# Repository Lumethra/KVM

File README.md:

# KVM
## What is this?

Its a KVM, just there is a catch, it should be a KM, because it doesnt fulfill the criterias for the "V". A KVM is a device that can let you switch the connected USB-devices from one PC to another, so just press or toggle the switch and your mouse and keyboard are connected to the other device, for example a laptop. KVM stands for Keyboard, Video, Mouse and since my thingi only supports USB-devices it only supports keyboards, mice and maybe other usb devices. Thats also why I would call it a KM. 

### Features:
  - 2 USB-C-upstreams
      - for the 2 PC's
  - 4 USB-downstreams
      - 2 USB-C
      - 2 USB-A
  - 1 SL2.1S to bundle the 4 downstreams into 2 pins (D+, D-)
  - 1 Mux to switch between the 2 upstreams for PC switching
  - 1 slider, toggle, switch kinda thingi to set the state

---

## Why?

I thought it would be funny to try that out. It turned out to be quite easy. I also thought about USB3.0 and even USB4.0, but that was too complicated and I settled on USB2.0. A KVM is also sth that you can use in your daily workflow and could turn out to be really handy. 

---

## How??

It was simply replicating the USB-Hub, which I made for my keebs and connecting the upstream to the mux which handles the switching between the 2 USB-C(2.0) to archieve the switching between devices. 

---

## Renders 
> enjoy the raytracing

| PCB with Components | 
| --- |
|  |
|  |

| PCB without Components |
| --- |
|  |
|  |

---

## PCB + Schematics

| Schematics |
| --- |
|  |

| PCB |
| --- |
|  |

---

<details>
  <summary>
    <h2>Zine</h2>
  </summary>

| Zine |
| --- |
|  |

  ---
</details>

## BOM

| Part | Purpose | Cost | Quantity | Total Cost | LCSC/JLCPCB Number | Link |
| --- | --- | --- | --- | --- | --- | --- |
| PCB |connect everything together | $2 | 1(5) | $2 | ~ | [JLCPCB](https://jlcpcb.com) |
| Capacitors | reduce noise in the power | $0.0032 | 8 | $0.0256 | C15849, C14663 | [C15849](https://jlcpcb.com/partdetail/C15849) / [C14663](https://jlcpcb.com/partdetail/C14663) |
| Resistors | prevent things go boom | $0.0016 | 8 | $0.0138 | C23186, C23206 | [C23186](https://jlcpcb.com/partdetail/C23186),[C23206](https://jlcpcb.com/partdetail/C23206) |
| Toggle Switch | say which computer | $0.0579 | 1 | $0.0579 | C431541 | [JLCPCB](https://jlcpcb.com/partdetail/C431541)  |
| USB Mux | change computer (USB) | $0.3720 | 1 | $0.3720 | C42407092 | [JLCPCB](https://jlcpcb.com/partdetail/C42407092)  |
| USB Hub | bundle the downstream | $0.2258 | 1 | $0.2258 | C2684433 | [JLCPCB](https://jlcpcb.com/partdetail/C2684433)  |
| UCB-C | usb connectors | $0.0740 | 4 | $0.2960 | C2765186 | [JLCPCB](https://jlcpcb.com/partdetail/C2765186)  |
| USB-A | usb connectors big | $0.0636 | 2 | $0.1272 | C668591 | [JLCPCB](https://jlcpcb.com/partdetail/C668591)  |

> the prices can change depending on the provider and time <br>
> you can find the JLCPCB parts on [LCSC](https://lcsc.com/) too (exept the PCB) <br>

---

## Contribute

Want to add something?? Want a real KVM with Video? Found any bugs?? Feel free to open a PR (pull request) or an issue. 
> the libraries are all imported with [easyeda2kicad](https://github.com/uPesy/easyeda2kicad.py)

---

## Thank you

A huge thank you to my brain, who didnt die in this session. Another huge thank you to all the guys teaching me hardware. A last thank you to my laptop and kicad who dont like each other and decides to crash alot.

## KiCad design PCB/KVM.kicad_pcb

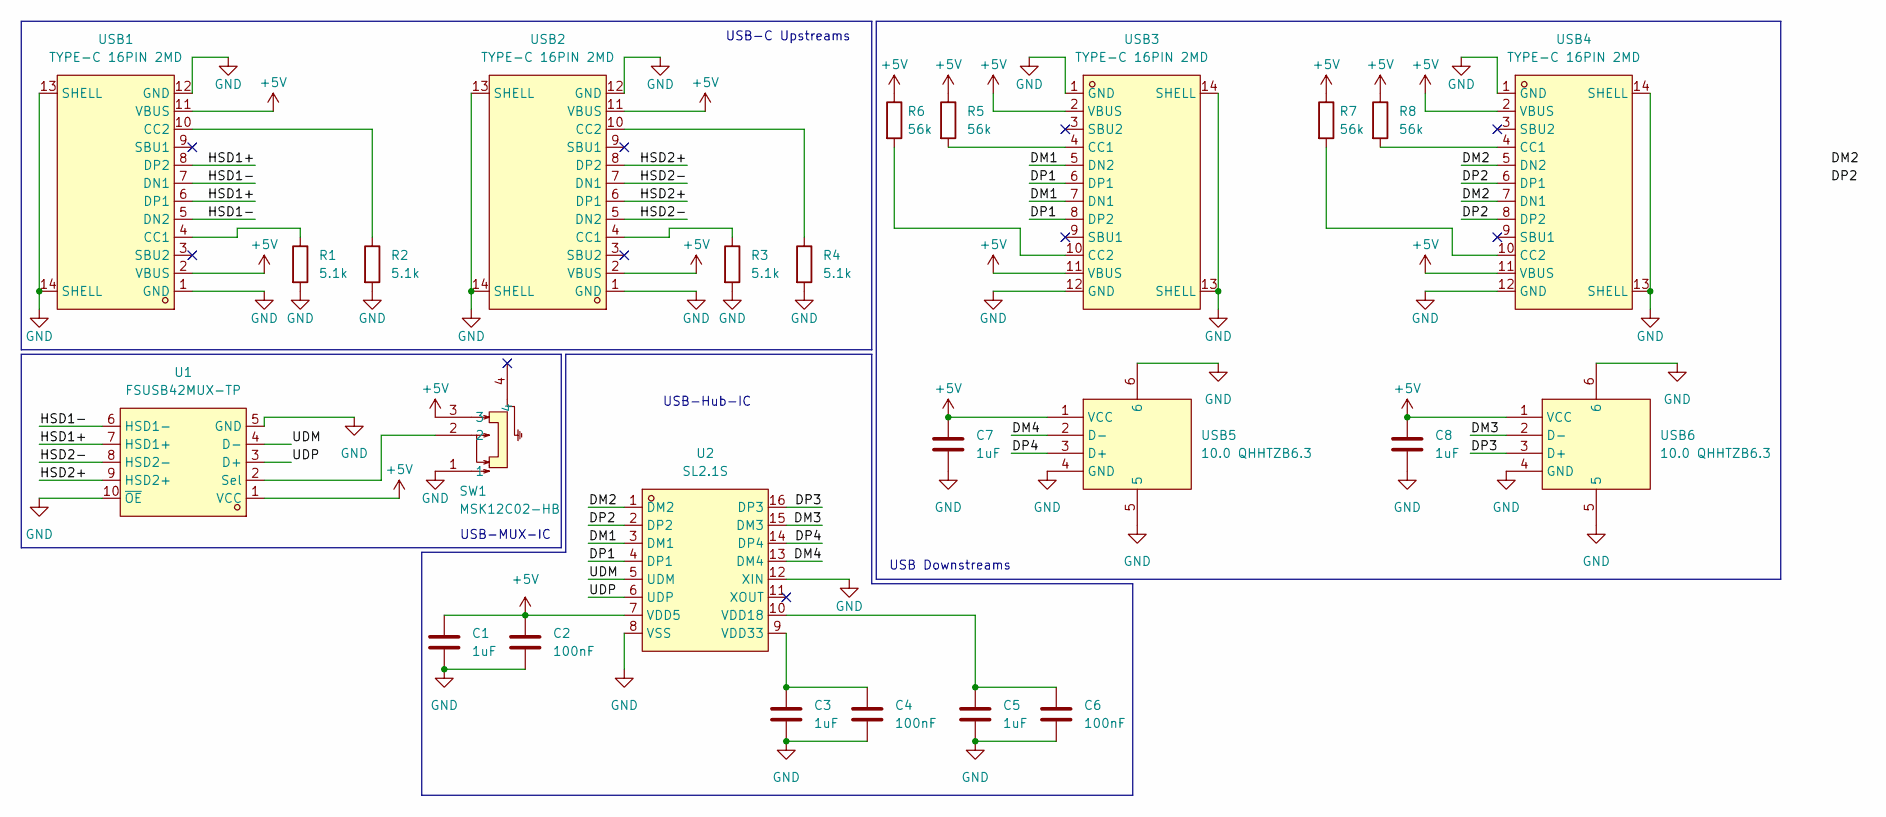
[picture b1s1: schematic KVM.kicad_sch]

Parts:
C1, C3, C5, C7, C8: 1uF; C_0603_1608Metric; LCSC Part C15849
C2, C4, C6: 100nF; C_0603_1608Metric; LCSC Part C14663
R1, R2, R3, R4: 5.1k; R_0603_1608Metric; LCSC Part C23186
R5, R6, R7, R8: 56k; R_0603_1608Metric; LCSC Part C23206
SW1: MSK12C02-HB; SW-TH_MSK12C02-HB-1; MPN MSK12C02-HB; LCSC Part C431541
U1: FSUSB42MUX-TP; MSOP-10_L3.0-W3.0-P0.50-LS4.9-BL; MPN FSUSB42MUX-TP; LCSC Part C42407092
U2: SL2.1S; SSOP-16_L4.6-W2.6-P0.53-LS4.0-BL; MPN SL2.1s; LCSC Part C2684433
USB1, USB2, USB3, USB4: TYPE-C 16PIN 2MD; USB-C-SMD_TYPE-C-6PIN-2MD-073; MPN TYPE-C 16PIN 2MD(073); LCSC Part C2765186
USB5, USB6: 10.0 QHHTZB6.3; USB-A-TH_10.0QHHTZB6.3; MPN 10.0 QHHTZB6.3; LCSC Part C668591

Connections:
+5V: C1.1, C2.1, C7.1, C8.1, R5.1, R6.1, R7.1, R8.1, SW1.3, U1.1 (VCC), U2.7 (VDD5), USB1.2 (VBUS), USB1.11 (VBUS), USB2.2 (VBUS), USB2.11 (VBUS), USB3.2 (VBUS), USB3.11 (VBUS), USB4.2 (VBUS), USB4.11 (VBUS), USB5.1 (VCC), USB6.1 (VCC)
/DM1: U2.3 (DM1), USB3.5 (DN2), USB3.7 (DN1)
/DM2: U2.1 (DM2), USB4.5 (DN2), USB4.7 (DN1)
/DM3: U2.15 (DM3), USB6.2 (D-)
/DM4: U2.13 (DM4), USB5.2 (D-)
/DP1: U2.4 (DP1), USB3.6 (DP1), USB3.8 (DP2)
/DP2: U2.2 (DP2), USB4.6 (DP1), USB4.8 (DP2)
/DP3: U2.16 (DP3), USB6.3 (D+)
/DP4: U2.14 (DP4), USB5.3 (D+)
/HSD1+: U1.7 (HSD1+), USB1.6 (DP1), USB1.8 (DP2)
/HSD1-: U1.6 (HSD1-), USB1.5 (DN2), USB1.7 (DN1)
/HSD2+: U1.9 (HSD2+), USB2.6 (DP1), USB2.8 (DP2)
/HSD2-: U1.8 (HSD2-), USB2.5 (DN2), USB2.7 (DN1)
/UDM: U1.4 (D-), U2.5 (UDM)
/UDP: U1.3 (D+), U2.6 (UDP)
GND: C1.2, C2.2, C3.2, C4.2, C5.2, C6.2, C7.2, C8.2, R1.2, R2.2, R3.2, R4.2, SW1.1, U1.5 (GND), U1.10 (~OE), U2.8 (VSS), U2.12 (XIN), USB1.1 (GND), USB1.12 (GND), USB1.13 (SHELL), USB1.14 (SHELL), USB2.1 (GND), USB2.12 (GND), USB2.13 (SHELL), USB2.14 (SHELL), USB3.1 (GND), USB3.12 (GND), USB3.13 (SHELL), USB3.14 (SHELL), USB4.1 (GND), USB4.12 (GND), USB4.13 (SHELL), USB4.14 (SHELL), USB5.4 (GND), USB5.5, USB5.6, USB6.4 (GND), USB6.5, USB6.6
unnamed: SW1.2, U1.2 (Sel)
unnamed: C5.1, C6.1, U2.10 (VDD18)
unnamed: C3.1, C4.1, U2.9 (VDD33)
unnamed: R1.1, USB1.4 (CC1)
unnamed: R2.1, USB1.10 (CC2)
unnamed: R3.1, USB2.4 (CC1)
unnamed: R4.1, USB2.10 (CC2)
unnamed: R5.2, USB3.4 (CC1)
unnamed: R6.2, USB3.10 (CC2)
unnamed: R8.2, USB4.4 (CC1)
unnamed: R7.2, USB4.10 (CC2)

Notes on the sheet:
USB-MUX-IC
USB-Hub-IC
USB-C Upstreams
USB Downstreams

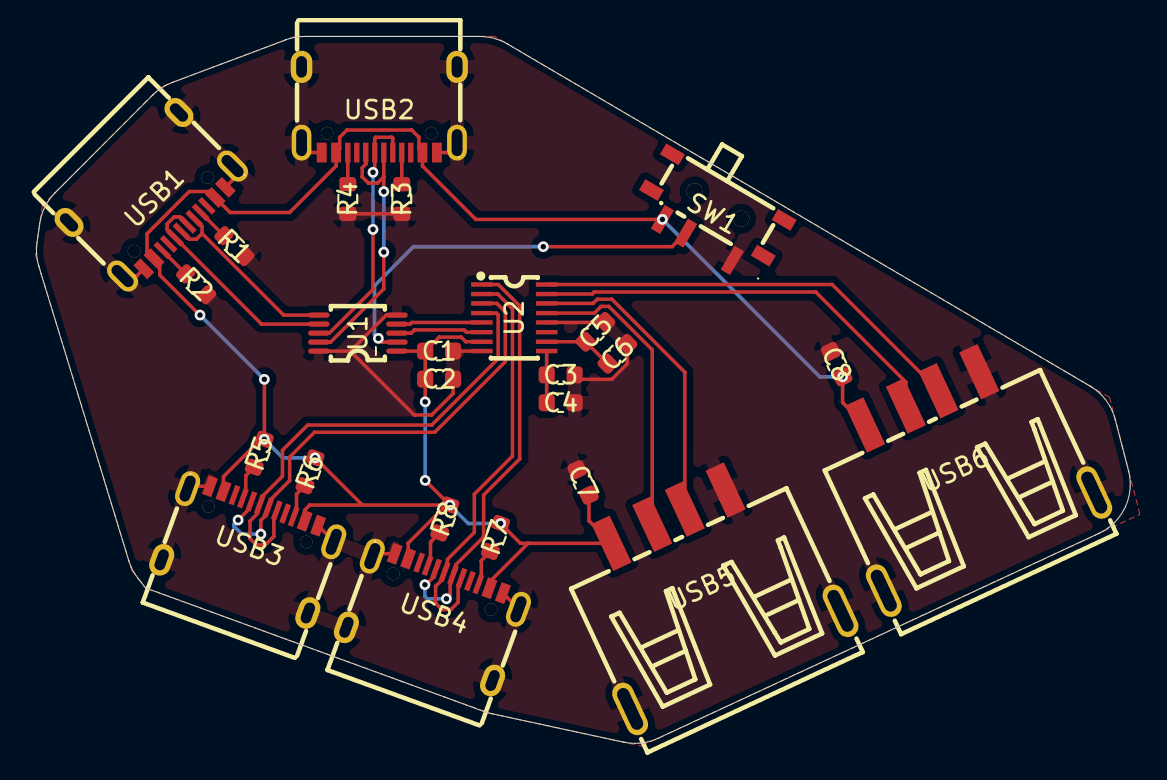
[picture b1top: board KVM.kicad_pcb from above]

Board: 2 copper layers, 60.8 x 39.3 mm, 25 parts (0 on the bottom side), 27 nets.

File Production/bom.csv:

Name,Designator,Footprint,Quantity,Value,Price,LCSC Part #,Purchase Link
Capacitors 1uF,"C1, C3, C5, C7, C8",0603,5,1uF,$0.0032,C15849,https://jlcpcb.com/partdetail/C15849
Capacitors 100nF,"C2, C4, C6",0603,3,100nF,$0.0032,C14663,https://jlcpcb.com/partdetail/C14663
Resistors 5.1k,"R1, R2, R3, R4",0603,4,5.1k,$0.0016,C23186,https://jlcpcb.com/partdetail/C23186
Resistors 56k,"R5, R6, R7, R8",0603,4,56k,$0.0016,C23206,https://jlcpcb.com/partdetail/C23206
Toggle Switch,SW1,SW-TH_MSK12C02-HB-1,1,MSK12C02-HB,$0.0579,C431541,https://jlcpcb.com/partdetail/C431541
USB Mux,U1,MSOP-10_L3.0-W3.0-P0.50-LS4.9-BL,1,FSUSB42MUX-TP,$0.3720,C42407092,https://jlcpcb.com/partdetail/C42407092
USB Hub,U2,SSOP-16_L4.6-W2.6-P0.53-LS4.0-BL,1,SL2.1S,$0.2258,C2684433,https://jlcpcb.com/partdetail/C2684433
USB-C Connector,"USB1, USB2, USB3, USB4",USB-C-SMD_TYPE-C-6PIN-2MD-073,4,TYPE-C 16PIN 2MD,$0.0740,C2765186,https://jlcpcb.com/partdetail/C2765186
USB-A Connector,"USB5, USB6",USB-A-TH_10.0QHHTZB6.3,2,10.0 QHHTZB6.3,$0.0636,C668591,https://jlcpcb.com/partdetail/C668591

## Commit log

2026-06-12 adding images
2026-06-12 fixing bom and adding prod
2026-06-12 readme
2026-06-12 adding zine
